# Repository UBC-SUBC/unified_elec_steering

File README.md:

# unified_elec_steering

This repo contains the KiCad and Gerber files for the Unified Elec Steering system, which is being used in the 2022-2023 submarine.

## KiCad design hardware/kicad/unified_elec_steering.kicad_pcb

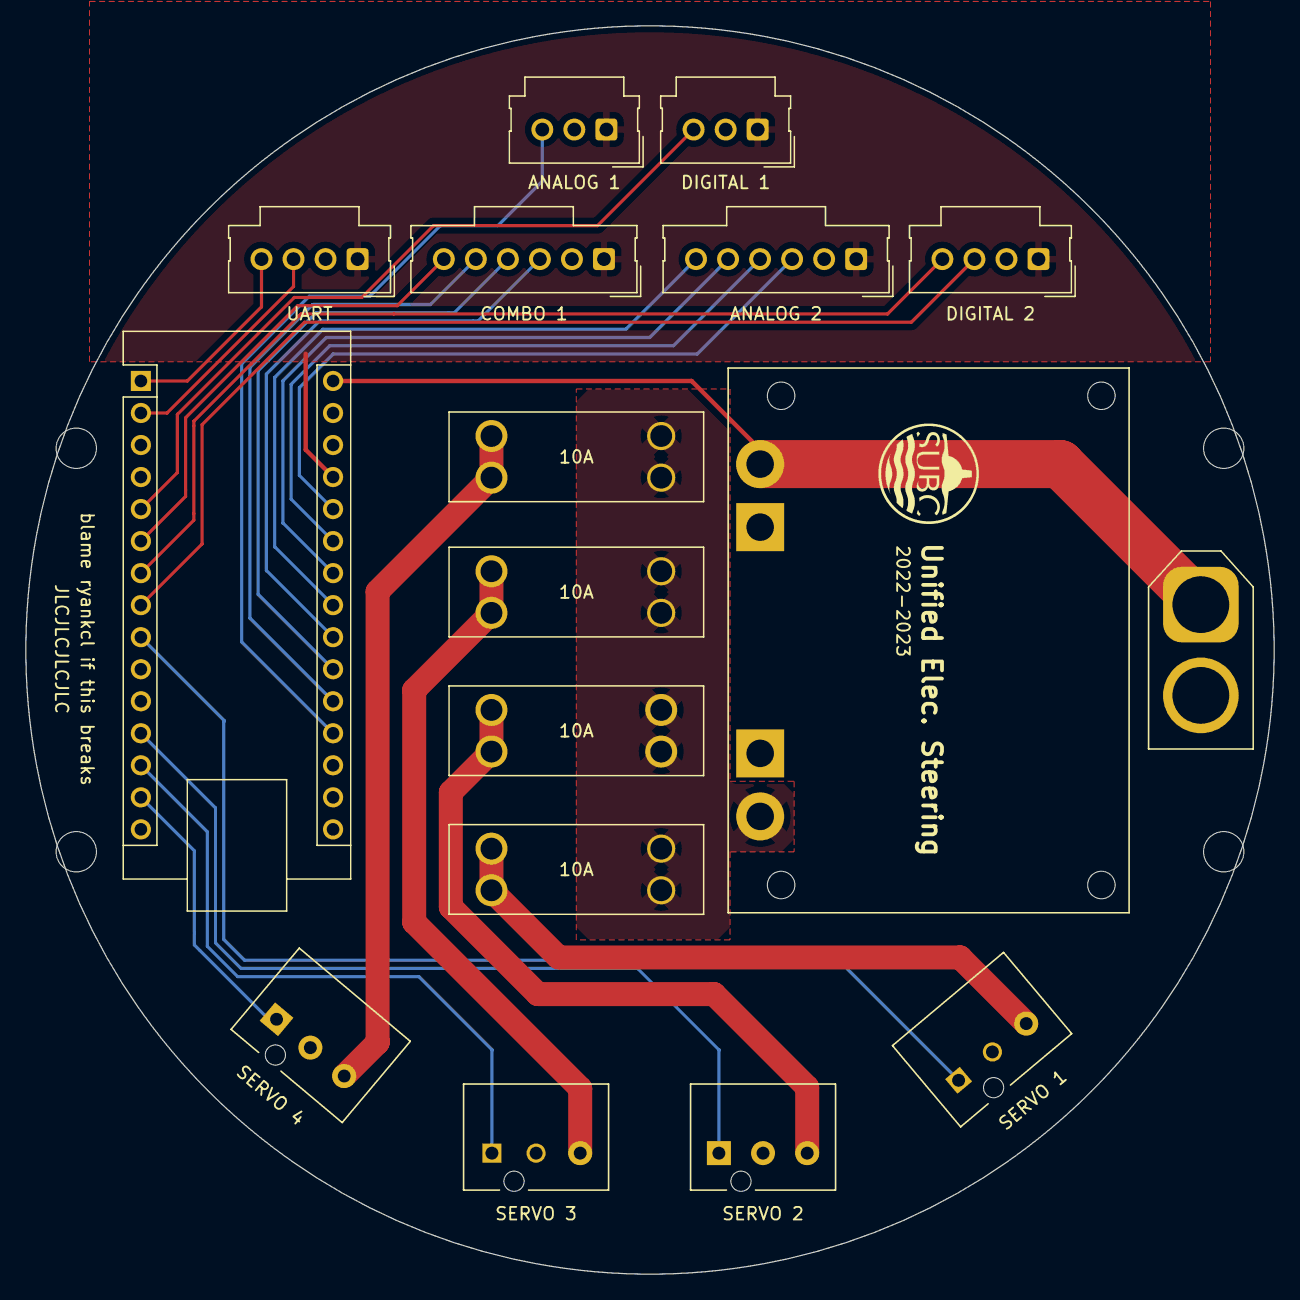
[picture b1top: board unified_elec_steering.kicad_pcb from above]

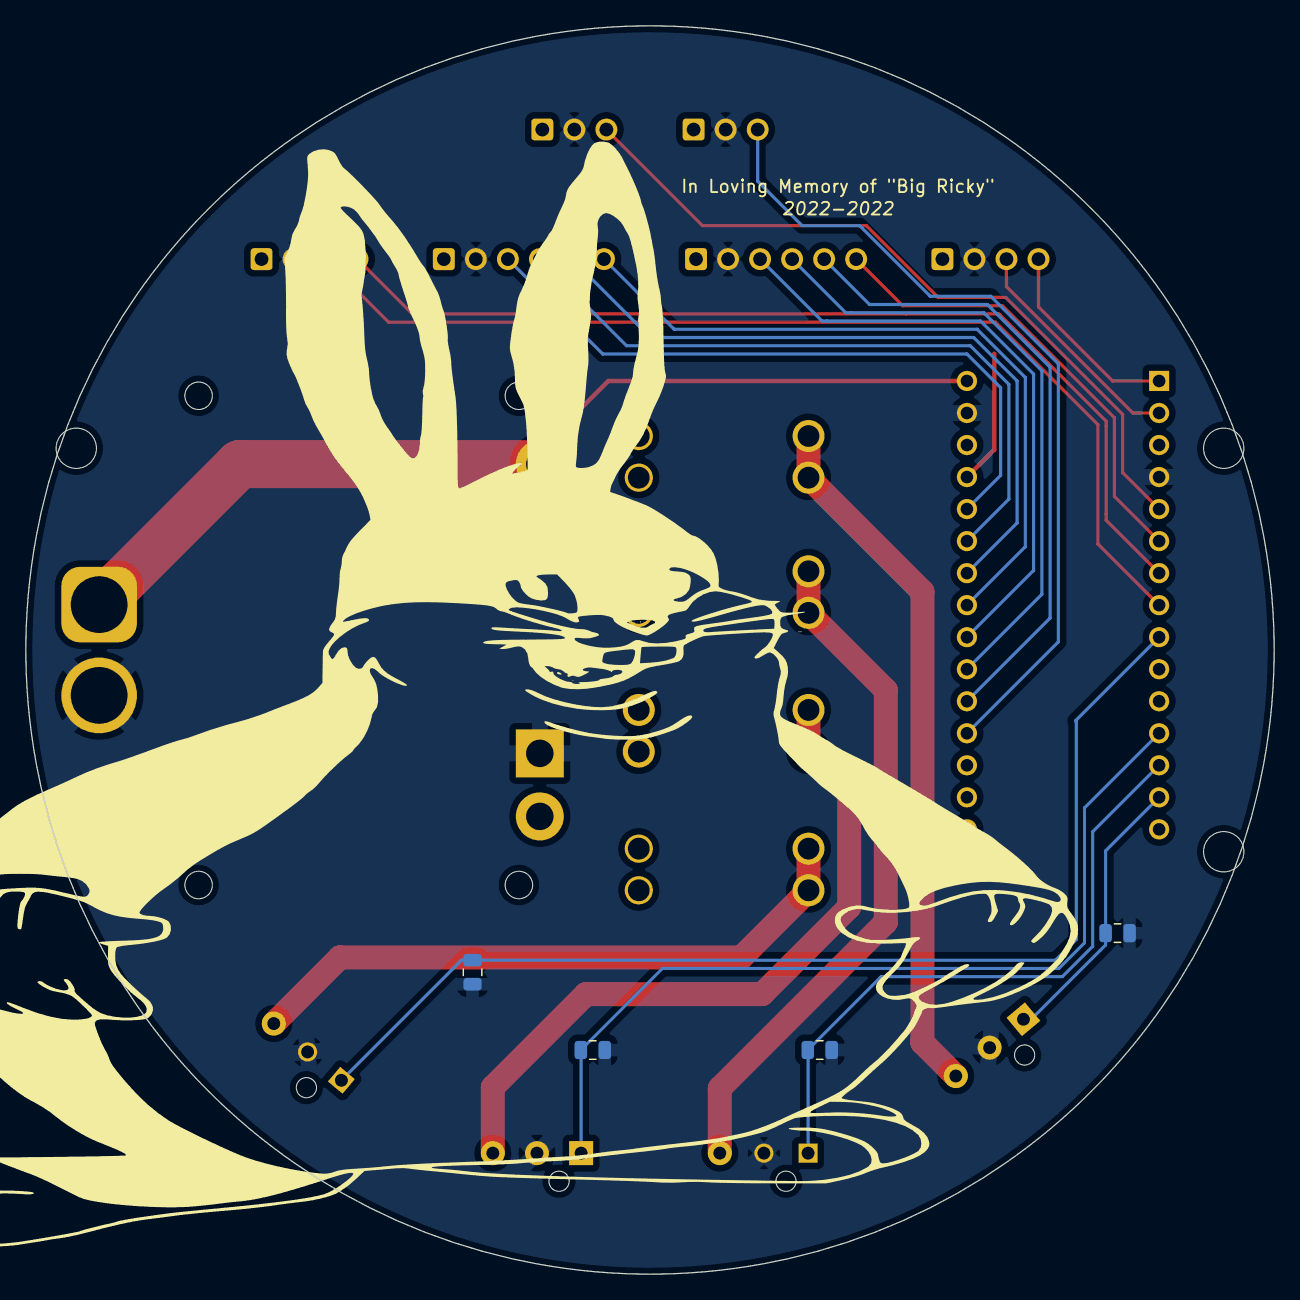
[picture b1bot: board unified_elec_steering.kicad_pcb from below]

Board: 2 copper layers, 99.0 x 99.0 mm, 21 parts (4 on the bottom side), 26 nets.

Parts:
C1, C2, C3, C4: C_0805_2012Metric
F1, F2, F3, F4: Fuse; 3557-2
J3: Conn_01x02; AMASS_XT60-M_1x02_P7.20mm_Vertical
J4, J5, J9, J10: Conn_01x03; 1722861103
J6, J12: Conn_01x04; Molex_SL_171971-0004_1x04_P2.54mm_Vertical
J7, J8: Conn_01x06; Molex_SL_171971-0006_1x06_P2.54mm_Vertical
J11, J13: Conn_01x03; Molex_SL_171971-0003_1x03_P2.54mm_Vertical
U1: Arduino_Nano_v3.x; Arduino_Nano
U2: D24V150F7

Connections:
+5V: J6.1, J7.1, J8.1, J11.1, J12.1, J13.1, U1.27 (+5V)
+7.5V: F1.2, F2.2, F3.2, F4.2, U2.4 (MOD)
A0: J13.3, U1.19 (A0)
A1: J8.5, U1.20 (A1)
A2: J8.4, U1.21 (A2)
A3: J8.3, U1.22 (A3)
A4: J7.6, U1.23 (A4)
A5: J7.5, U1.24 (A5)
A6: J7.4, U1.25 (A6)
A7: J7.3, U1.26 (A7)
D2: J11.3, U1.5 (D2)
D3: J8.6, U1.6 (D3)
D4: J12.4, U1.7 (D4)
D5: J12.3, U1.8 (D5)
GND: C1.2, C2.2, C3.2, C4.2, J3.2, J4.2, J5.2, J6.2, J7.2, J8.2, J9.2, J10.2, J11.2, J12.2, J13.2, U1.4 (GND), U1.29 (GND), U2.2 (GND), U2.3 (PG)
unnamed: F1.1, J4.3
unnamed: F2.1, J9.3
unnamed: F3.1, J5.3
unnamed: F4.1, J10.3
RX: J6.3, U1.2 (D0/RX)
SERVO0: C1.1, J10.1, U1.9 (D6)
SERVO1: C2.1, J9.1, U1.12 (D9)
SERVO2: C3.1, J5.1, U1.13 (D10)
SERVO3: C4.1, J4.1, U1.14 (D11)
TX: J6.4, U1.1 (D1/TX)
VBUS: J3.1, U1.30 (VIN), U2.1 (VIN)

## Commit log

2022-10-05 Initial hardware commit
2022-10-05 Fix schematic layout
2022-10-05 Fix 3dmodels path
2022-10-05 Update gerber files
2022-10-29 Update PCB after review
2023-01-21 Initial commit of circle PCB
2023-01-21 Fix GND spoke width
2023-02-04 add mounting holes
